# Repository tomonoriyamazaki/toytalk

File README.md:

# toytalk
SS Bootcamp 3rd #2025

## プロジェクト
- 声をかけると返答してくれるAIおもちゃの作成
- 目的は親の時間確保
- 子供がおもちゃに夢中になると同時に、言葉のキャッチボール力の向上もできたらうれしい
- OpenAIのAPIを利用するため、会話のたびに料金が発生する
- APIキーを発行してセットすれば、課金分のみの利用が可能
- APIキーの設定が面倒であれば、月額課金でも利用できる
- 無料で使用することも可能。会話はできないが、ただおうむ返しをしたり、事前にセットした昔話を話してくれる、という機能もあると親としては助かる（実際はサーバー維持費用かかるので検討中）
- おもちゃイメージ　「まねっこぴょこぴょこアンパンマン」
  - https://www.amazon.co.jp/gp/product/B0B4RQ85ZQ/ref=sw_img_1?smid=AN1VRQENFRJN5&th=1

## 音声会話のしくみ
  1. STT（音声→テキスト）
  2. LLM
  3. TTS（テキスト→音声）

前提として
  - OpenAIのAPIキーが必要。API利用のたびに課金が発生する
  - 音声処理はスマホ側で行うため、スマホアプリが必要。課金状況の確認などもアプリで行う

## PJの流れ
- デモサイト構築：マイク→音声→テキスト→LLM→音声返答してくれるサイトを作る　→6月完了
- ラズパイに落とし込む　→7月完了
- スマホアプリを作って、スマホと連動させる
- おもちゃとしてデザインを決めて形にする
- →一旦ここまで出来たらうれしい

サービス化するなら
- 何よりも応答速度が課題：デモサイト上では1往復で5秒前後かかる。すべての処理が直列なのと、サーバーレス構成のためと思われる　→　一旦解決。初回応答まで安定して2秒程度に短縮できた。しかもサーバーレス
  - STT：ここが足を引っ張っているように感じる。websocket通信で高速化できないか検討中　※ここをブラウザのテキスト化機能にしたら（つまりSSTをなくしたら）、往復で1-4秒と速度アップした
  - LLM：4.1-miniを利用。かなり早いはず
  - TTS：回答内容をまとめてmp3にしている？ためか長文だと時間かかるように感じる。子供向けということで、LLMの回答内容をシンプルにすることで短縮できないか
  - ※最悪難しかったら、待ってる間に「相槌を打つ」機能の追加を検討。「そうだね～」、「なるほどね」、「ふむふむ」とかいろいろなパターンを使って時間を稼げないか検討
  - →OpenAIのRealTime APIを使えば、SST→LLM→TTSをリアルタイム&並列化できるため爆速になる。ただ、これには2つのデメリットがある
    - 利用料が高い
    - ボイスをカスタマイズ（キャラクター化）できない
  - この対策として、以下が考えられる
    - STT、LLM、TTSそれぞれ、Stream対応のAPIを利用して、自前でWebRTC環境を整備する
    - TTS（ボイス化）についてはさらにカスタマイズできるものを選ぶ　※Microsoft EdgeTTSが有力
    - 一方で開発が長引く可能性が高いので、どこまで対応するか線引きが必要になりそう
    - 一旦、動作が安定してる現状のサーバーレス構成で進めて、RealTime API利用など検証しつつ落としどころを探る
  - 20250901：速度問題は一旦解決。サーバーレス構成（Lambda）でも、LLM/TTSをストリーム処理することで、話初めの速度を改善できた。STTは現在スマホ側で処理しているので、スマホによって性能の差がある可能性あり
  - 20251005：STTも解決。Soniox STTで一時キーを発行することで、クライアント⇔Soniox間で直接やり取りする。認証は別途必要だが速度には大きく影響しない想定。これで、STT→LLM→TTSの並列化ができ、応答も2秒程度となった
- 音声の精度を高める（くしゃみとか物音も拾ってしまう）　→　スマホでなら問題なし。くしゃみとかキーボードなら拾わない
- アプリ上で課金管理をできるようにする
- 過去の会話を踏まえて会話する機能。3-5つくらいまで保持しして、あとは要約するとか工夫できないか（会話積み重ねると重くなる）　→　実装済み
- APIキー管理の仕組みを設計・実装
- 会話保持、振り返り機能の実装
- 無料で利用する場合のおうむ返し機能、昔話をしてくれる機能の設計・実装
- ボイスとテンションを子供向けにする　→　いろいろなTTSを試しているが、なかなかない。リアルタイム性 + キャラっぽいのがあまりない。ニジボイスは申請中

## デモサイト　※対応済み
- https://toytalk.zakicorp.com/demo/index.html

### レビューいただいてからの修正点まとめ
- 音声を検知するまで何もしない処理にする
- キャラクター入れる
- アニメーション入れる
- キャラクター選択できる
  - 画像をそれぞれ用意する
- 処理時間を表示させる
- 会話ボタンを押したらずっと会話する　※キャンセルボタンないが、一旦再読み込みでキャンセルとなる
- 今までの会話を保持しながら話す
- iPhoneでも音声出力できるようにする
- デモサイトの構成図

### メモ：セキュリティ観点で本番は以下の設定が必要
| 設定項目                               | 開発中 | 本番             |
| ---------------------------------- | --------- | ------------------------------ |
| `Access-Control-Allow-Credentials` | （なし）      | `true`（必要なら）                   |
| CloudFront キャッシュキー                 | （特になし）    | `Origin` を含めて設定                |
| APIキーの保護                 | Lambda環境変数    | Secrets Manager利用（チーム開発でなければ必須ではない）      |

## マイコン化について
- ラズパイだとおもちゃの価格が跳ね上がる。価格を抑えるためにはマイコン化が必要
- マイコン化すると、ラズパイと比べスペックがかなり落ちて機能も制限される
- そのため、おもちゃはマイク/スピーカーの中継にして、BlueTooth/wifiでスマホと連携して、スマホ側で音声処理をする構成にする
- そうすると、スマホアプリ起動が前提になるので、親としては子供がおもちゃと会話している間はスマホを操作できなくなってしまう可能性がある
- アプリをバックグラウンド起動させて対応できないか検討中　※最悪、親がスマホを触る際は、会話モード以外（オウム返しや一方的な話）で楽しんでもらう
- [ToyTalkマイコン実装はこちら](docs/mcu.md)

## ラズパイ対応 ver1　※対応済み
- デモサイトでやってること（ブラウザ部分）をラズパイに置き換えるだけ

- マイク/スピーカーはUSBタイプのものをそれぞれ用意してラズパイに装着
- VADは簡単なものを実装。咳や物音といった短い音を無視（0.4秒以内の音声は検知しない）
- 音声を流している間は、割り込みのマイク入力はoff　※ありだとスピーカーの音をマイクが拾う、の無限ループになるため。マイコン化を考えると制御の難易度が高そう
- 今後の課題も同じく、返答速度・声がメイン
  - 速度：①base64処理とmp3/wavの処理最適化、②システムプロンプトを会話特化に、③相槌機能追加（Lambdaの2重化）で、改善&カバーを検討
  - 声：今のOpenAI APIでチューニングしつつ、別のTTS用APIを検討

## ラズパイ対応 ver2　※対応済み
- スマホアプリ（一旦iOS）を作り、アプリ側で音声処理を行う。ラズパイはマイク/スピーカーの中継だけ（マイコン化に向けた対応）

- このあたりで速度改善、VAD、声のチューニングの本格対応を始める？マイコン化を優先？
- 一旦速度改善できた。Lambdaのストリーミング処理でLLM/TTSをそれぞれ並列化。STT（VADも）は一旦スマホ側で処理。今後SSTもサーバー側へ移行する
- iOSアプリのインストール（TestFlifhtというアプリも必要）：https://testflight.apple.com/join/Aq5D8b62
- [ToyTalkアプリ実装はこちら](app/README.md)
- 調査進めたところ、アプリ経由でなくても、おもちゃ（ESP32 s3という安価なマイコン）⇔中継サーバーで直接やりとりできそう。ver2の構成はとりやめて、ver3の構成にする

## ラズパイ対応 ver3　※対応済み
- SST（音声のテキスト化）をサーバー側に移行する　→　実装済み
- アプリによるラズパイへのwifi設定は実装していないが、マイコン化が実現できそうなのでそちらを優先で対応する

## マイコン対応　※対応中
- スマホアプリを経由せず、マイコン⇔API基盤（STT + LLM + STT）で音声会話できるか検証
- wifi設定もアプリからできるようにする

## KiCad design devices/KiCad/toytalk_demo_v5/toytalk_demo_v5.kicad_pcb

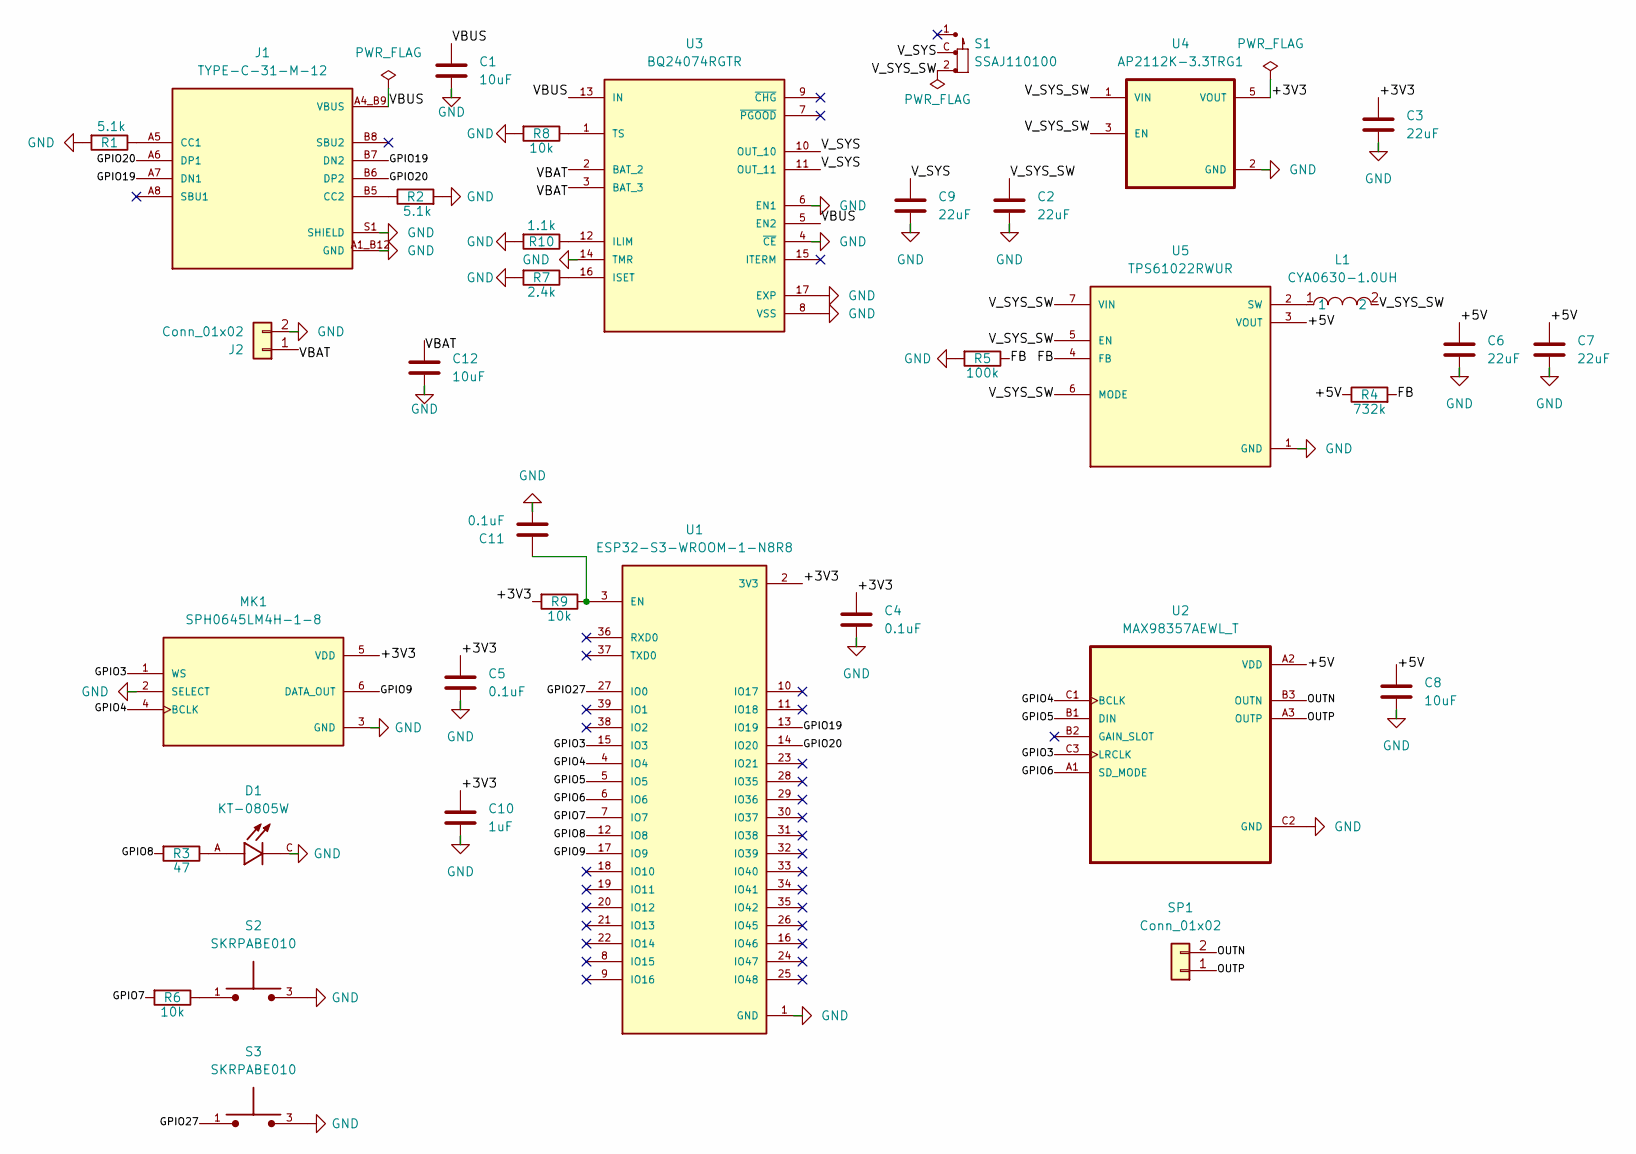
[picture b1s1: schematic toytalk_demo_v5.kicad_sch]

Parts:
C1, C8, C12: 10uF; C_0603_1608Metric
C2, C3, C6, C7, C9: 22uF; C_0603_1608Metric
C4, C5, C11: 0.1uF; C_0603_1608Metric
C10: 1uF; C_0603_1608Metric
D1: KT-0805W; LED_KT-0805W; PARTREV 2017.05.16
J1: TYPE-C-31-M-12; HRO_TYPE-C-31-M-12; PARTREV 2020.12.08
J2: Conn_01x02; PinHeader_1x02_P2.54mm_Vertical
L1: CYA0630-1.0UH; IND-SMD_L7.2-W6.6_GPSR0730; LCSC Part C5189744
MK1: SPH0645LM4H-1-8; MIC_SPH0645LM4H-B
R1, R2: 5.1k; R_0603_1608Metric
R3: 47; R_0603_1608Metric
R4: 732k; R_0603_1608Metric
R5: 100k; R_0603_1608Metric
R6, R8, R9: 10k; R_0603_1608Metric
R7: 2.4k; R_0603_1608Metric
R10: 1.1k; R_0603_1608Metric
S1: SSAJ110100; SW_SSAJ110100; PARTREV N/A
S2, S3: SKRPABE010; SW_SKRPABE010
SP1: Conn_01x02; PinHeader_1x02_P2.54mm_Vertical
U1: ESP32-S3-WROOM-1-N8R8; XCVR_ESP32S3WROOM1N8R8
U2: MAX98357AEWL_T; BGA9N40P3X3_134X143X69N
U3: BQ24074RGTR; QFN50P300X300X100-17N; PARTREV M
U4: AP2112K-3.3TRG1; SOT95P285X140-5N; PARTREV 2-2
U5: TPS61022RWUR; CONV_TPS61022RWUR; PARTREV 4223724/C 02/2018

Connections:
/+3V3: C3.1, C4.1, C5.1, C10.1, MK1.5 (VDD), R9.2, U1.2 (3V3), U4.5 (VOUT)
/+5V: C6.1, C7.1, C8.1, R4.1, U2.A2 (VDD), U5.3 (VOUT)
/FB: R4.2, R5.1, U5.4 (FB)
/GPIO3: MK1.1 (WS), U1.15 (IO3), U2.C3 (LRCLK)
/GPIO4: MK1.4 (BCLK), U1.4 (IO4), U2.C1 (BCLK)
/GPIO5: U1.5 (IO5), U2.B1 (DIN)
/GPIO6: U1.6 (IO6), U2.A1 (SD_MODE)
/GPIO7: R6.2, U1.7 (IO7)
/GPIO8: R3.2, U1.12 (IO8)
/GPIO9: MK1.6 (DATA_OUT), U1.17 (IO9)
/GPIO19: J1.A7 (DN1), J1.B7 (DN2), U1.13 (IO19)
/GPIO20: J1.A6 (DP1), J1.B6 (DP2), U1.14 (IO20)
/GPIO27: S3.1, S3.2, U1.27 (IO0)
/OUTN: SP1.2, U2.B3 (OUTN)
/OUTP: SP1.1, U2.A3 (OUTP)
/VBAT: C12.1, J2.1, U3.2 (BAT_2), U3.3 (BAT_3)
/V_SYS: C9.1, S1.C, U3.10 (OUT_10), U3.11 (OUT_11)
/V_SYS_SW: C2.1, L1.2, S1.2, U4.1 (VIN), U4.3 (EN), U5.5 (EN), U5.6 (MODE), U5.7 (VIN)
GND: C1.2, C2.2, C3.2, C4.2, C5.2, C6.2, C7.2, C8.2, C9.2, C10.2, C11.2, C12.2, D1.C, J1.A1_B12 (GND), J1.B1_A12 (GND), J1.S1 (SHIELD), J1.S2 (SHIELD), J1.S3 (SHIELD), J1.S4 (SHIELD), J2.2, MK1.2 (SELECT), MK1.3 (GND), R1.2, R2.2, R5.2, R7.2, R8.2, R10.2, S2.3, S2.4, S3.3, S3.4, U1.1 (GND), U1.40 (GND), U1.41_1 (GND), U1.41_2 (GND), U1.41_3 (GND), U1.41_4 (GND), U1.41_5 (GND), U1.41_6 (GND), U1.41_7 (GND), U1.41_8 (GND), U1.41_9 (GND), U2.C2 (GND), U3.4 (~CE), U3.6 (EN1), U3.8 (VSS), U3.14 (TMR), U3.17 (EXP), U4.2 (GND), U5.1 (GND)
unnamed: D1.A, R3.1
unnamed: J1.A5 (CC1), R1.1
unnamed: J1.B5 (CC2), R2.1
unnamed: R6.1, S2.1, S2.2
unnamed: C11.1, R9.1, U1.3 (EN)
unnamed: R10.1, U3.12 (ILIM)
unnamed: R7.1, U3.16 (ISET)
unnamed: R8.1, U3.1 (TS)
unnamed: L1.1, U5.2 (SW)
VBUS: C1.1, J1.A4_B9 (VBUS), J1.B4_A9 (VBUS), U3.5 (EN2), U3.13 (IN)

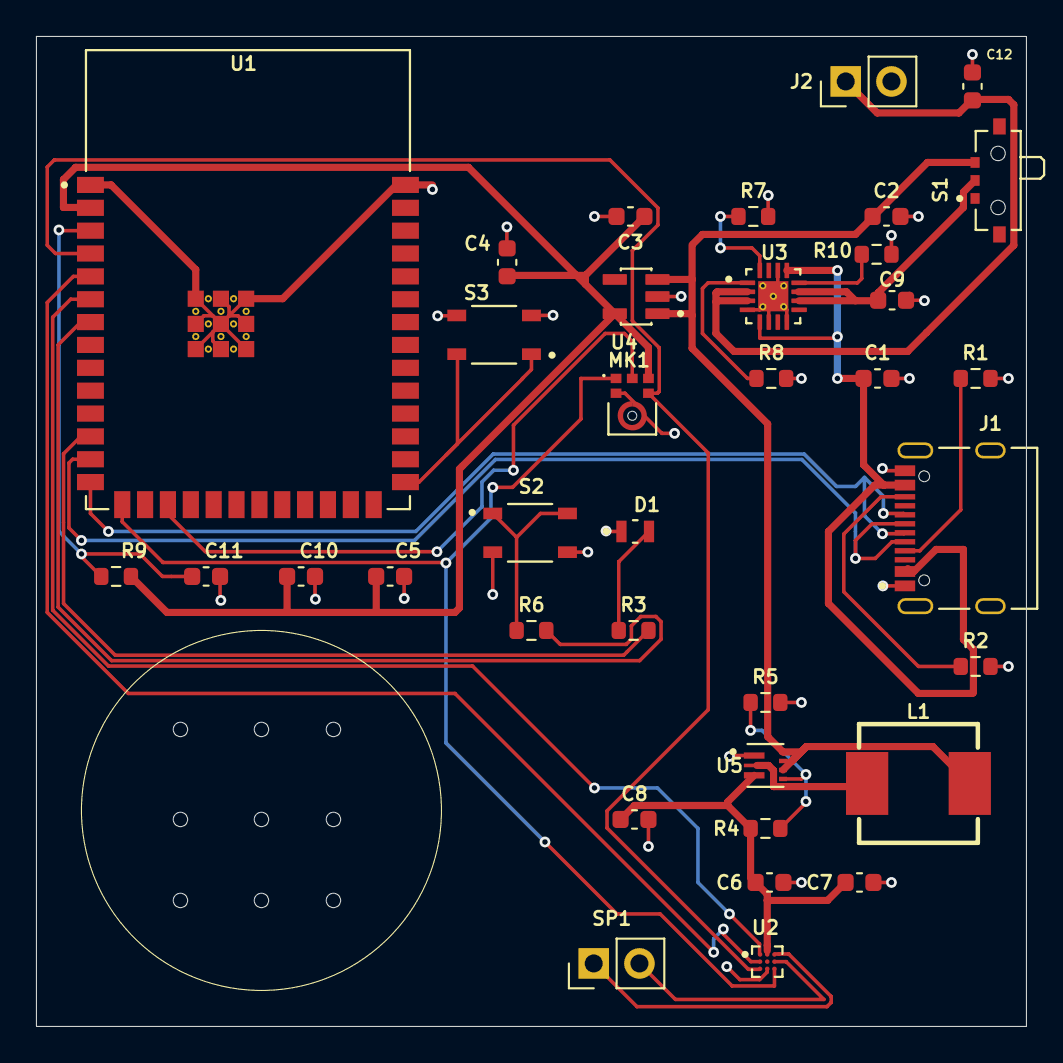
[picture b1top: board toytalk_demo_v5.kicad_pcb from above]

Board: 2 copper layers, 55.0 x 55.0 mm, 36 parts (0 on the bottom side), 29 nets.

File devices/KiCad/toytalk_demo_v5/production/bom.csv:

Designator,Footprint,Quantity,Value,LCSC Part #
"C1, C12, C8",0603,3,10uF,
C10,0603,1,1uF,
"C11, C4, C5",0603,3,0.1uF,
"C2, C3, C6, C7, C9",0603,5,22uF,
D1,LED_KT-0805W,1,KT-0805W,
J1,HRO_TYPE-C-31-M-12,1,TYPE-C-31-M-12,
L1,IND-SMD_L7.2-W6.6_GPSR0730,1,CYA0630-1.0UH,C5189744
MK1,MIC_SPH0645LM4H-B,1,SPH0645LM4H-1-8,
"R1, R2",0603,2,5.1k,
R10,0603,1,1.1k,
R3,0603,1,47,
R4,0603,1,732k,
R5,0603,1,100k,
"R6, R8, R9",0603,3,10k,
R7,0603,1,2.4k,
S1,SW_SSAJ110100,1,SSAJ110100,
"S2, S3",SW_SKRPABE010,2,SKRPABE010,
U1,XCVR_ESP32S3WROOM1N8R8,1,ESP32-S3-WROOM-1-N8R8,
U2,BGA9N40P3X3_134X143X69N,1,MAX98357AEWL_T,
U3,QFN50P300X300X100-17N,1,BQ24074RGTR,
U4,SOT95P285X140-5N,1,AP2112K-3.3TRG1,
U5,CONV_TPS61022RWUR,1,TPS61022RWUR,

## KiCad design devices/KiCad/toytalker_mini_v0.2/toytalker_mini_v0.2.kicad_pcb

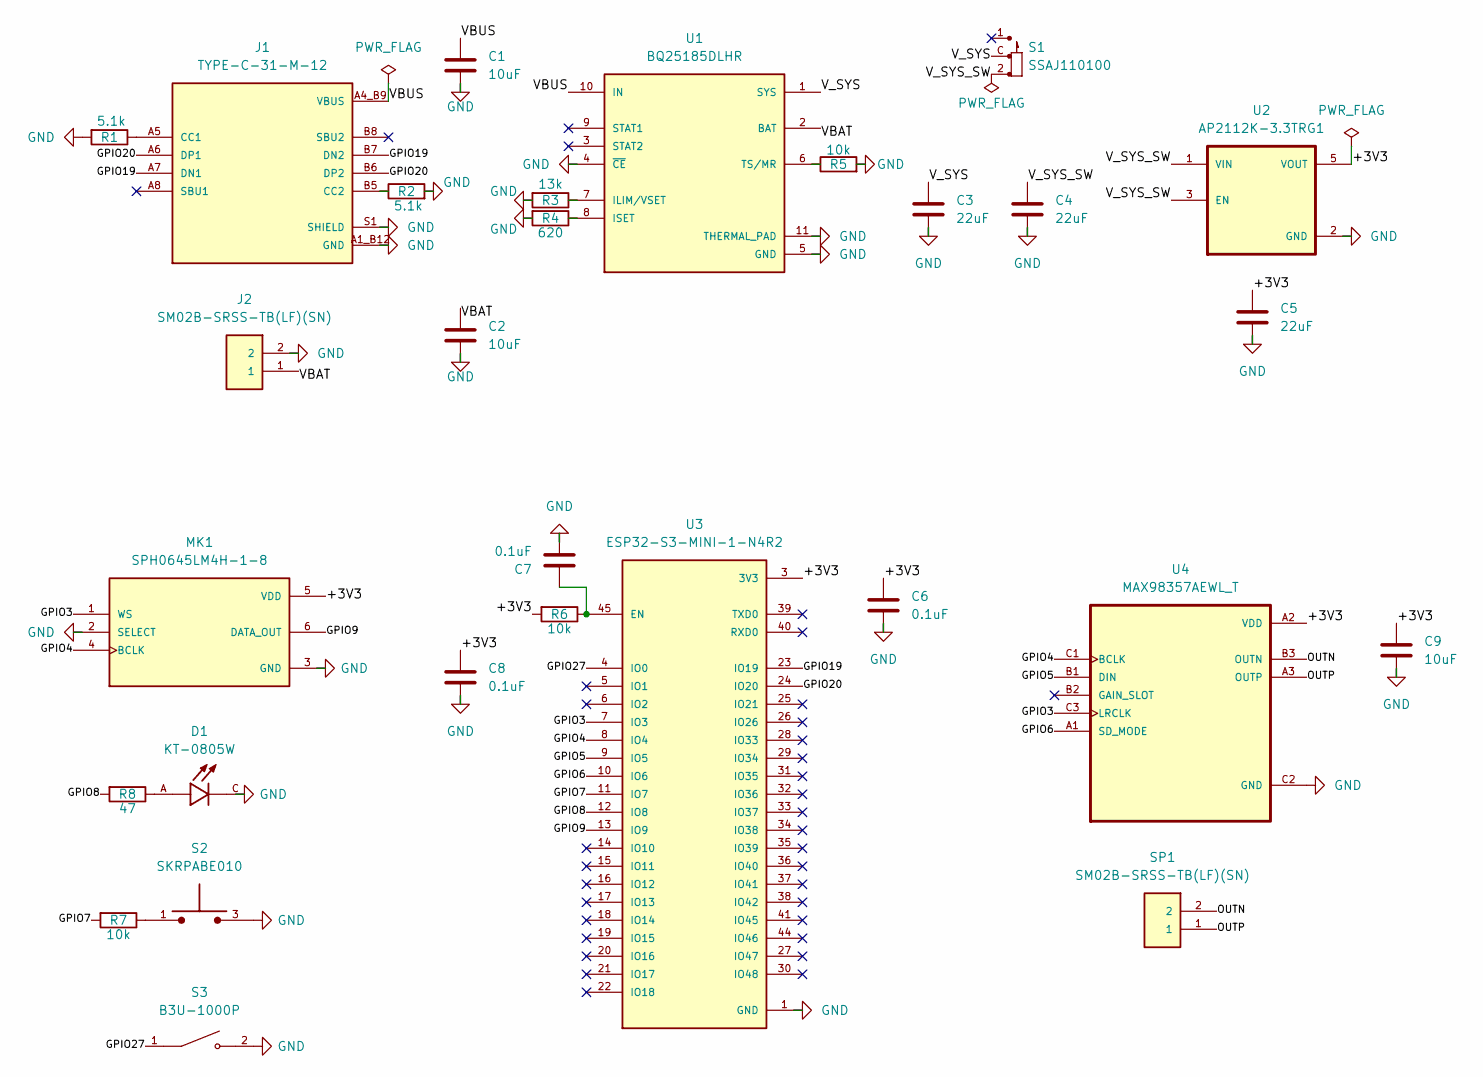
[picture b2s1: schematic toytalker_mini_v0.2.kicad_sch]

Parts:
C1, C2, C9: 10uF; C_0603_1608Metric
C3, C4, C5: 22uF; C_0603_1608Metric
C6, C7, C8: 0.1uF; C_0402_1005Metric
D1: KT-0805W; LED_KT-0805W; PARTREV 2017.05.16
J1: TYPE-C-31-M-12; HRO_TYPE-C-31-M-12; PARTREV 2020.12.08
J2: SM02B-SRSS-TB(LF)(SN); SM02B-SRSS-TB_LF__SN_
MK1: SPH0645LM4H-1-8; MIC_SPH0645LM4H-B
R1, R2: 5.1k; R_0402_1005Metric
R3: 13k; R_0402_1005Metric
R4: 620; R_0402_1005Metric
R5, R6, R7: 10k; R_0402_1005Metric
R8: 47; R_0402_1005Metric
S1: SSAJ110100; SW_SSAJ110100; PARTREV N/A
S2: SKRPABE010; SW_SKRPABE010
S3: B3U-1000P; SW_SPST_B3U-1000P
SP1: SM02B-SRSS-TB(LF)(SN); SM02B-SRSS-TB_LF__SN_
U1: BQ25185DLHR; IC_BQ25185DLHR; PARTREV OCTOBER 2023
U2: AP2112K-3.3TRG1; SOT95P285X140-5N; PARTREV 2-2
U3: ESP32-S3-MINI-1-N4R2; XCVR_ESP32-S3-MINI-1-N4R2; PARTREV v0.6
U4: MAX98357AEWL_T; BGA9N40P3X3_134X143X69N

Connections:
/+3V3: C5.1, C6.1, C8.1, C9.1, MK1.5 (VDD), R6.2, U2.5 (VOUT), U3.3 (3V3), U4.A2 (VDD)
/GPIO3: MK1.1 (WS), U3.7 (IO3), U4.C3 (LRCLK)
/GPIO4: MK1.4 (BCLK), U3.8 (IO4), U4.C1 (BCLK)
/GPIO5: U3.9 (IO5), U4.B1 (DIN)
/GPIO6: U3.10 (IO6), U4.A1 (SD_MODE)
/GPIO7: R7.2, U3.11 (IO7)
/GPIO8: R8.2, U3.12 (IO8)
/GPIO9: MK1.6 (DATA_OUT), U3.13 (IO9)
/GPIO19: J1.A7 (DN1), J1.B7 (DN2), U3.23 (IO19)
/GPIO20: J1.A6 (DP1), J1.B6 (DP2), U3.24 (IO20)
/GPIO27: S3.1, U3.4 (IO0)
/OUTN: SP1.2, U4.B3 (OUTN)
/OUTP: SP1.1, U4.A3 (OUTP)
/VBAT: C2.1, J2.1, U1.2 (BAT)
/V_SYS: C3.1, S1.C, U1.1 (SYS)
/V_SYS_SW: C4.1, S1.2, U2.1 (VIN), U2.3 (EN)
GND: C1.2, C2.2, C3.2, C4.2, C5.2, C6.2, C7.2, C8.2, C9.2, D1.C, J1.A1_B12 (GND), J1.B1_A12 (GND), J1.S1 (SHIELD), J1.S2 (SHIELD), J1.S3 (SHIELD), J1.S4 (SHIELD), J2.2, MK1.2 (SELECT), MK1.3 (GND), R1.2, R2.2, R3.2, R4.2, R5.2, S2.3, S2.4, S3.2, U1.4 (~CE), U1.5 (GND), U1.11 (THERMAL_PAD), U2.2 (GND), U3.1 (GND), U3.2 (GND), U3.42 (GND), U3.43 (GND), U3.46 (GND), U3.47 (GND), U3.48 (GND), U3.49 (GND), U3.50 (GND), U3.51 (GND), U3.52 (GND), U3.53 (GND), U3.54 (GND), U3.55 (GND), U3.56 (GND), U3.57 (GND), U3.58 (GND), U3.59 (GND), U3.60 (GND), U3.61 (GND), U3.61_1 (GND), U3.61_2 (GND), U3.61_3 (GND), U3.61_4 (GND), U3.61_5 (GND), U3.61_6 (GND), U3.61_7 (GND), U3.61_8 (GND), U3.62 (GND), U3.63 (GND), U3.64 (GND), U3.65 (GND), U4.C2 (GND)
unnamed: D1.A, R8.1
unnamed: J1.A5 (CC1), R1.1
unnamed: J1.B5 (CC2), R2.1
unnamed: R7.1, S2.1, S2.2
unnamed: R3.1, U1.7 (ILIM/VSET)
unnamed: R4.1, U1.8 (ISET)
unnamed: R5.1, U1.6 (TS/MR)
unnamed: C7.1, R6.1, U3.45 (EN)
VBUS: C1.1, J1.A4_B9 (VBUS), J1.B4_A9 (VBUS), U1.10 (IN)

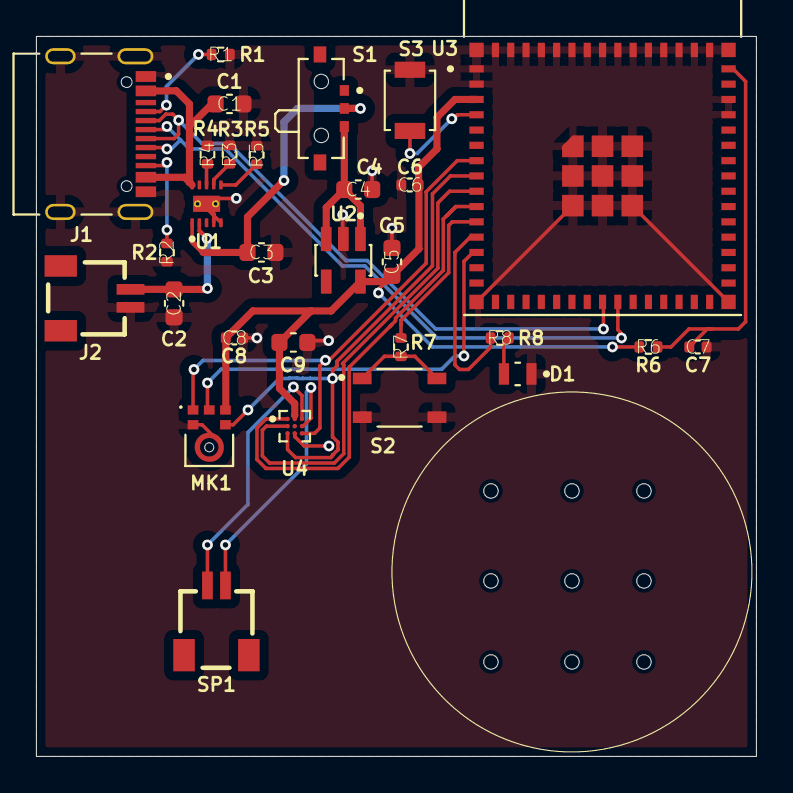
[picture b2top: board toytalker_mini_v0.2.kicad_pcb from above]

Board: 2 copper layers, 40.0 x 40.0 mm, 29 parts (0 on the bottom side), 26 nets.

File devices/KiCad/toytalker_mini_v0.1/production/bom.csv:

Designator,Footprint,Quantity,Value,LCSC Part #
"C1, C2, C9",0603,3,10uF,
"C3, C4, C5",0603,3,22uF,
"C6, C7, C8",0402,3,0.1uF,
D1,LED_KT-0805W,1,KT-0805W,
J1,HRO_TYPE-C-31-M-12,1,TYPE-C-31-M-12,
"J2, SP1",SM02B-SRSS-TB_LF__SN_,2,SM02B-SRSS-TB(LF)(SN),
MK1,MIC_SPH0645LM4H-B,1,SPH0645LM4H-1-8,
"R1, R2",0402,2,5.1k,
R3,0402,1,13k,
R4,0402,1,620,
"R5, R6, R7",0402,3,10k,
R8,0402,1,47,
S1,SW_SSAJ110100,1,SSAJ110100,
S2,SW_SKRPABE010,1,SKRPABE010,
S3,SW_SPST_B3U-1000P,1,B3U-1000P,
U1,IC_BQ25185DLHR,1,BQ25185DLHR,
U2,SOT95P285X140-5N,1,AP2112K-3.3TRG1,
U3,XCVR_ESP32-S3-MINI-1-N4R2,1,ESP32-S3-MINI-1-N4R2,
U4,BGA9N40P3X3_134X143X69N,1,MAX98357AEWL_T,

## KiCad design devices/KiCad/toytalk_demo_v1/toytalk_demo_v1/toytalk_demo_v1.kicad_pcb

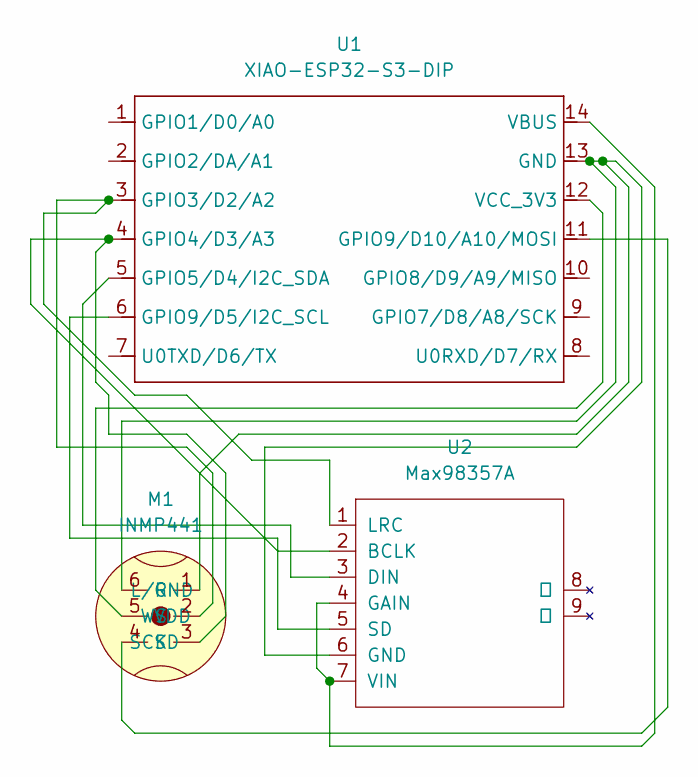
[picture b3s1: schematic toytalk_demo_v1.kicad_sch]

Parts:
M1: INMP441; INMP441_OMNIDIRECTIONAL_MICROPHONE_MODULE
U1: XIAO-ESP32-S3-DIP; XIAO-ESP32S3-DIP
U2: Max98357A; MAX98357-MODULE SMD FOOTPRINT

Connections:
unnamed: M1.1 (L/R), M1.6 (GND), U1.13 (GND), U2.6 (GND)
unnamed: M1.3 (SCK), U1.4 (GPIO4/D3/A3), U2.2 (BCLK)
unnamed: M1.4 (SD), U1.11 (GPIO9/D10/A10/MOSI)
unnamed: M1.5 (VDD), U1.12 (VCC_3V3)
unnamed: M1.2 (WS), U1.3 (GPIO3/D2/A2), U2.1 (LRC)
unnamed: U1.5 (GPIO5/D4/I2C_SDA), U2.3 (DIN)
unnamed: U1.6 (GPIO9/D5/I2C_SCL), U2.5 (SD)
unnamed: U1.14 (VBUS), U2.4 (GAIN), U2.7 (VIN)

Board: 2 copper layers, 3 parts (0 on the bottom side), 8 nets, no tracks yet.

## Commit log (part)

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2025-07-20 Add files via upload
    ラズパイ側に配置するpython（ブラウザ相当）と、ラズパイ用のLambdaコード
2025-08-30 modify all folder and add react native app
2025-08-30 modify app/README.md
2025-08-30 make pilot ios app for test flight
2025-08-30 modify app for TestFlight
2025-08-30 modify icon
2025-08-30 submit testflight
2025-08-31 test stream lambda
2025-08-31 update stream lambda
2025-08-31 update stream lambda for gpt-5-mini
2025-08-31 update stream lambda for gpt-4.1-mini
2025-08-31 update stream lambda for gpt-4.1-mini add chank
2025-08-31 update stream lambda for gpt-4.1-mini stream first step
2025-08-31 update stream lambda for gpt-4.1-mini stop emit debug test
2025-08-31 update stream lambda for gpt-4.1-mini clean but input text is same
2025-08-31 update stream lambda for gpt-4.1-mini clean without input voice
2025-08-31 update stream lambda for gpt-4.1-mini clean without input voice increment build number
2025-09-01 update ios app for clean conversasion ver 0.3.0 and add PhotoLibrary Usage by testflight error
2025-09-06 add debug time
2025-09-06 add saving talk history
2025-09-07 add header and choosing model #only display
2025-09-07 add choosing model for lambda #only display
2025-09-07 add choosing model ready complete
2025-09-07 add choosing Open AI voice
2025-09-07 enable using Google TTS voice
2025-09-07 modify Google TTS speaking init noise, enable setting parameters
2025-09-07 enable using Gemini Speech Generation
2025-09-29 ver 0.4.2 add debug mode and modify history
2025-09-29 ver0.5.0 add STT setting only
2025-09-29 ver0.5.0 ready soniox STT coding
2025-09-29 ver0.5.0 create soniox temporary key get lambda
2025-09-30 ver0.5.0 create stt process but the voice doesn't play after the second time
2025-10-01 ver0.5.0 create soniox stt process but the voice doesn't play after the second time only soniox
2025-10-01 ver0.5.0 create soniox stt process but the voice doesn't play after the second time only soniox but can output voice after the third time
2025-10-01 ver0.5.0 create soniox stt process but the voice doesn't play after the second time only soniox2
2025-10-02 ver0.5.0 create soniox stt process but the voice a little bit unsteable
2025-10-02 ver0.5.0 create soniox stt process but the voice is fail only the second time2
2025-10-02 ver0.5.0 create soniox stt process but the voice is fail only the second time3 : clean code
2025-10-03 ver0.5.0 create soniox stt process but the voice is fail only the second time5 : clean code
2025-10-03 ver0.5.0 create soniox stt process but the voice is fail only the second time6 : delete no need file
2025-10-03 chore: stop tracking router.d.ts
2025-10-03 modify gitignore
2025-10-03 ver0.5.0 create soniox stt process but the voice is fail only the second time : clean code:before change expo-av to expo-audio
2025-10-03 ver0.5.0 add expo-audit for stt but dirty code
2025-10-04 temporary test usage , fix: deactivate AVAudioSession on stop in react-native-audio-record
2025-10-04 temporary test usage but doesn't work
2025-10-04 temporary test usage , somtething hint
2025-10-04 before modify sst temporary key process
2025-10-04 ver0.5.1 modify soniox stt process but the second voice doesn't work
2025-10-04 ver0.5.1 modify convesation history
2025-10-04 ver0.5.1 display realtime soniox stt text
2025-10-05 ver0.5.2 bug fix soniox stt
2025-10-05 ver0.5.2 bug fix soniox stt --complete
2025-10-05 ver0.5.3 speed up stt
2025-10-05 ver0.5.3 modify local stt display input sentence
2025-10-05 ver0.5.4 modify local stt display input sentence --complete
2025-10-05 ver0.5.5 auto record mode restart for only soniox stt
2025-10-05 ver0.5.5 auto record mode restart on soniox/local stt
2025-10-05 ver0.5.5 auto record mode restart on soniox/local stt --complete
2025-10-05 ver0.5.5 modify app.json
2025-10-05 ready for esp32 s3 coding
2025-10-09 create esp32 audio record script
2025-10-09 success esp32 audio wav record
2025-10-09 update esp32 audio wav record quality
2025-10-11 ok wifi setting on esp32
2025-10-11 ok websocket soniox stt straming on esp32
2025-10-11 modify websocket soniox stt straming on esp32
2025-10-12 modify audio.ino for adding speaker module on esp32
2025-10-12 ok test speaker module on esp32
2025-10-12 ok test mario melody for speaker module on esp32
2025-10-12 ok record -> speaker and coding demo_v1.ino
2025-10-13 before modify base64 -> pcm process
2025-10-25 test speaker
2025-11-15 ok test speaker_raw_pcm_sound
2025-11-15 ok 70% ok speaker_oepnAI_base64_pcm_sound but 30% noise exists
2025-11-15 ok 80% ok speaker_oepnAI_base64_pcm_sound but 20% noise exists, but maybe it is quolity limit
2025-11-15 ok base64 test speaker and before changing tts sketch
2025-11-16 before find past code
2025-11-16 add audio_speaker_tts_2
2025-11-16 modify audo_speaker_tts_2 for output every row
2025-11-16 modify audo_speaker_tts_2 : task is only conbine base64 chunk
2025-11-16 modify audo_speaker_tts_2 : complete conbine base64 chunk. before decoding base64 and output sound
2025-11-16 modify audo_speaker_tts_xxx : task is enable chunk base64 decode and play sound
2025-12-07 Add specific KiCad autosave file to gitignore
2026-01-04 Revert DMA buffer to 32 due to internal RAM constraints
2026-01-05 Fix LEDC API for Arduino-ESP32 v3.0+ compatibility
2026-01-05 Fix LED PWM polarity for correct on/off states
